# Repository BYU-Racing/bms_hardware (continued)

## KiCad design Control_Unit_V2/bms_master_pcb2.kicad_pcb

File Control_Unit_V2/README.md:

# BMS Control Unit V2 Files
This folder contains the KiCad project files for the BMS Control Unit V2.

PCB handoff from Rugby 11/10/2026 ☠️🌹⛓️

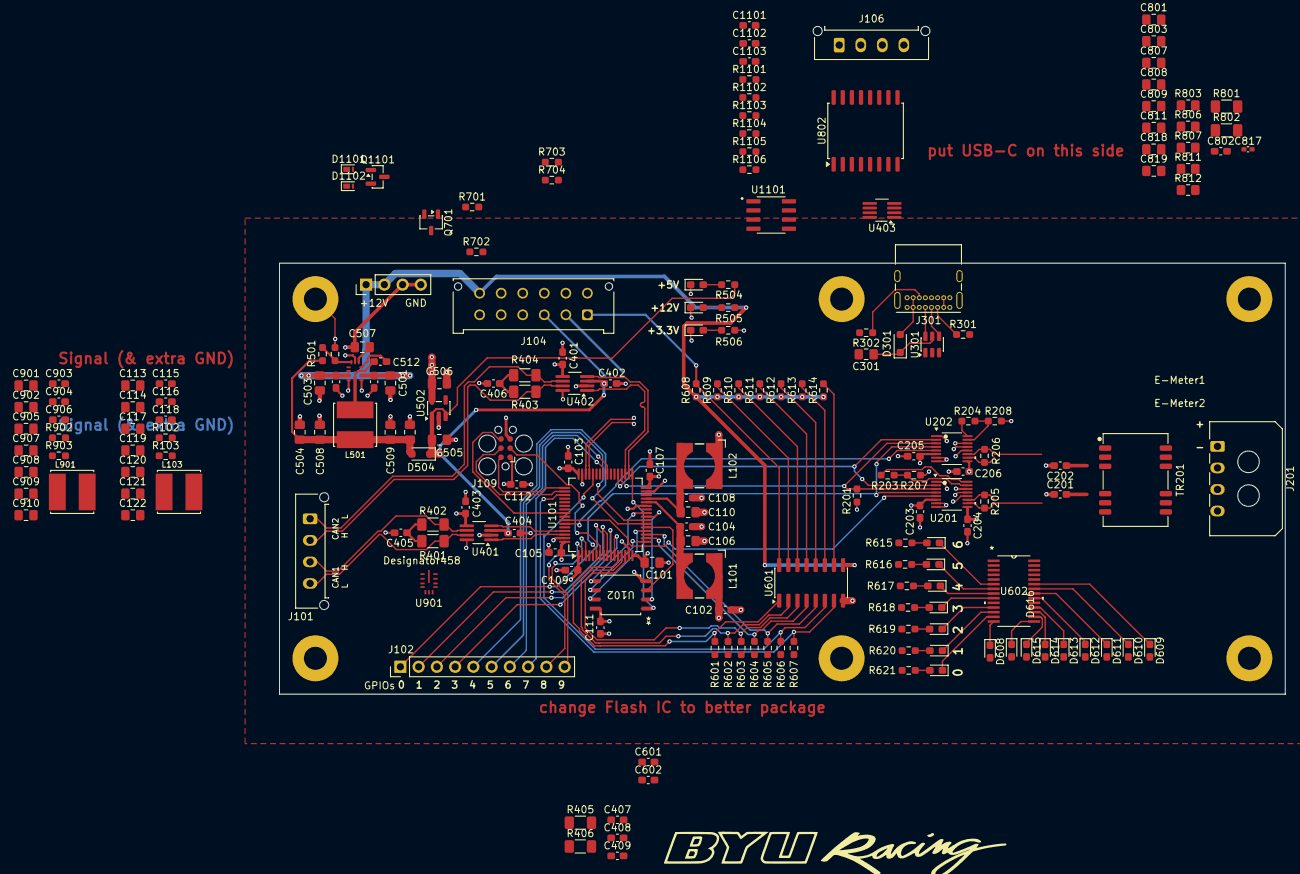
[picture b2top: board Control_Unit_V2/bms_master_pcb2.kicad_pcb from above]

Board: 4 copper layers, 140.0 x 60.0 mm, 197 parts (0 on the bottom side), 132 nets.

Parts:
C101: 4.7u; C_0805_2012Metric_Pad1.18x1.45mm_HandSolder
C102, C103, C104, C105, C107, C108, C109, C111, C112, C203, C204, C205, C206, C401, C402, C403, C404, C407, C408: 100n; C_0603_1608Metric_Pad1.08x0.95mm_HandSolder
C106, C110, C117, C505, C506, C507, C905: 1u; C_0805_2012Metric_Pad1.18x1.45mm_HandSolder
C113, C114, C301, C501, C503, C807, C818, C819, C901, C902: 10u; C_0805_2012Metric_Pad1.18x1.45mm_HandSolder
C115, C116, C510, C511, C903, C904: 220n; C_0603_1608Metric_Pad1.08x0.95mm_HandSolder
C118, C512, C906: 0.1u; C_0603_1608Metric_Pad1.08x0.95mm_HandSolder
C119, C120, C121, C122, C502, C504, C508, C509, C907, C908, C909, C910: 22u; C_0805_2012Metric_Pad1.18x1.45mm_HandSolder
C201, C202: 27p; C_0603_1608Metric_Pad1.08x0.95mm_HandSolder
C405, C406, C409, C802: 240p; C_0603_1608Metric_Pad1.08x0.95mm_HandSolder
C601: .1u; C_0603_1608Metric_Pad1.08x0.95mm_HandSolder
C602: 4.7u; C_0603_1608Metric_Pad1.08x0.95mm_HandSolder
C801, C803, C808: 100n; C_0805_2012Metric_Pad1.18x1.45mm_HandSolder
C809: 330p; C_0805_2012Metric_Pad1.18x1.45mm_HandSolder
C811: 2.2uF; C_0805_2012Metric_Pad1.18x1.45mm_HandSolder
C817: 0.1u; C_0402_1005Metric_Pad0.74x0.62mm_HandSolder
C1101: 21pf; C_0603_1608Metric_Pad1.08x0.95mm_HandSolder
C1102: 100nf; C_0603_1608Metric_Pad1.08x0.95mm_HandSolder
C1103: 0.1uf; C_0603_1608Metric_Pad1.08x0.95mm_HandSolder
D301, D504: 1N4448WS; D_SOD-323_HandSoldering
D501: 5V LED; LED_0603_1608Metric_Pad1.05x0.95mm_HandSolder
D502: 12V LED; LED_0603_1608Metric_Pad1.05x0.95mm_HandSolder
D503: 3.3V LED; LED_0603_1608Metric_Pad1.05x0.95mm_HandSolder
D601, D602, D603, D604, D605, D606, D607, D608, D609, D610, D611, D612, D613, D614, D615, D616: LED_Small; LED_0603_1608Metric_Pad1.05x0.95mm_HandSolder
D1101: Comchip ATV04A120J-HF; Nexperia_DSN1608-2_1.6x0.8mm
D1102: Vishay VTVS5V0ASMF-HM3-08; Nexperia_DSN1608-2_1.6x0.8mm
H101, H102, H103, H104, H105, H106: MountingHole; MountingHole_3.2mm_M3_Pad
J101, J106: CAN Connector; Molex_Micro-Fit_3.0_43650-0415_1x04_P3.00mm_Vertical
J102: GPIO; PinHeader_1x10_P2.54mm_Vertical
J103: EXTRA POWER IN; PinHeader_1x04_P2.54mm_Vertical
J104: Connector to GLV plug; Molex_Micro-Fit_3.0_43045-1212_2x06_P3.00mm_Vertical
J109: TC2030; Tag-Connect_TC2030-IDC-FP_2x03_P1.27mm_Vertical
J201: isoSPI Daisy Chain; Molex_Micro-Fit_3.0_43650-0400_1x04_P3.00mm_Horizontal
J301: USB4085-GF-A; USB_C_Receptacle_GCT_USB4085
L101, L102: 100u; WE-HEPC_6030
L103, L501, L901: 10u; IND_SRN6045TA-2R2Y
Q701: AO3400A; SOT-23-3
Q1101: 2N7002; SOT-23
R102, R501, R902: 100k; R_0603_1608Metric_Pad0.98x0.95mm_HandSolder
R103, R502, R903: 24.9k; R_0603_1608Metric_Pad0.98x0.95mm_HandSolder
R201, R1106: 2K; R_0603_1608Metric_Pad0.98x0.95mm_HandSolder
R203, R204, R207, R208, R506: 1k; R_0603_1608Metric_Pad0.98x0.95mm_HandSolder
R205, R206, R701: 100; R_0603_1608Metric_Pad0.98x0.95mm_HandSolder
R301, R302: 5.1K; R_0603_1608Metric_Pad0.98x0.95mm_HandSolder
R401, R402, R403, R404, R405, R406, R801, R802: 60; R_1206_3216Metric_Pad1.30x1.75mm_HandSolder
R504: 2.2k; R_0603_1608Metric_Pad0.98x0.95mm_HandSolder
R505, R615, R616, R617, R618, R619, R620, R621: 4.7k; R_0603_1608Metric_Pad0.98x0.95mm_HandSolder
R601, R602, R603, R604, R606, R607, R608, R609, R610, R611, R612, R613, R614, R702: 10K; R_0603_1608Metric_Pad0.98x0.95mm_HandSolder
R605: 720; R_0603_1608Metric_Pad0.98x0.95mm_HandSolder
R703: 470; R_0603_1608Metric_Pad0.98x0.95mm_HandSolder
R704: 100K; R_0603_1608Metric_Pad0.98x0.95mm_HandSolder
R803, R812: 10k; R_0805_2012Metric_Pad1.20x1.40mm_HandSolder
R806: 38k ±0.1%; R_0805_2012Metric_Pad1.20x1.40mm_HandSolder
R807: 10k ±0.1%; R_0805_2012Metric_Pad1.20x1.40mm_HandSolder
R811: 30k; R_0805_2012Metric_Pad1.20x1.40mm_HandSolder
R1101: 1.3K; R_0603_1608Metric_Pad0.98x0.95mm_HandSolder
R1102: 75K; R_0603_1608Metric_Pad0.98x0.95mm_HandSolder
R1103: 25K; R_0603_1608Metric_Pad0.98x0.95mm_HandSolder
R1104: 330R; R_0603_1608Metric_Pad0.98x0.95mm_HandSolder
R1105: 720R; R_0603_1608Metric_Pad0.98x0.95mm_HandSolder
TR201: TG110-E050N5xx; Transformer_HM0068ANL
U101: STM32G474RETx; LQFP-64_10x10mm_P0.5mm
U102: SST26VF064B-104V/MF; SOIJ8_SM_MCH
U201, U202: LTC6820HMS-TRPBF; MS_05-08-1669_ADI
U301: USBLC6-2SC6; SOT-23-6
U401, U402, U403: TCAN1044AVDDFRQ1; TSOT-23-8_HandSoldering
U502: AP2112K-3.3; SOT-23-5
U503, U901: LMR33620CQ5RNXRQ1; RNX0012B
U601: TPL7407LAD; SOIC-16_3.9x9.9mm_P1.27mm
U602: TLC59116IPWTQ1; PW28
U802: TJA1052i-1; SOIC-16W_7.5x10.3mm_P1.27mm
U1101: TLV9002QDRQ1; SOIC127P599X175-8N

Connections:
+3.3V: C101.1, C102.1, C103.1, C105.1, C107.1, C109.1, C111.1, C112.1, C203.1, C204.1, C205.1, C206.1, C401.1, C403.1, C407.1, C506.1, C1103.1, J104.2, J109.1, L101.1, L102.1, R201.2, R506.1, U101.1 (VBAT), U101.16 (VDD), U101.32 (VDD), U101.48 (VDD), U101.64 (VDD), U102.8 (VCC), U201.1 (EN), U201.6 (VDDS), U201.9 (VDD), U201.12 (MSTR), U202.1 (EN), U202.6 (VDDS), U202.9 (VDD), U202.12 (MSTR), U401.5 (VIO), U402.5 (VIO), U403.5 (VIO), U502.5 (VOUT), U602.28 (VCC), U1101.8 (V+)
+5V: C301.1, C402.1, C404.1, C408.1, C505.1, C803.1, C907.1, C908.1, C909.1, C910.1, D301.1 (K), D504.1 (K), L901.2, R504.1, R902.2, R1104.1, U301.5 (VBUS), U401.3 (VCC), U402.3 (VCC), U403.3 (VCC), U502.1 (VIN), U502.3 (EN), U802.1 (VDD1)
+5V_ISO: C119.1, C120.1, C121.1, C122.1, C801.1, J106.1, L103.2, R102.2, U802.11 (VDD2), U802.16 (VDD2)
+12V: C501.1, C503.1, C510.2, C511.2, C601.1, C602.1, C817.1, C818.2, C819.2, C901.1, C902.1, C903.2, C904.2, D601.2 (A), D602.2 (A), D603.2 (A), D604.2 (A), D605.2 (A), D606.2 (A), D607.2 (A), D608.2 (A), D609.2 (A), D610.2 (A), D611.2 (A), D612.2 (A), D613.2 (A), D614.2 (A), D615.2 (A), D616.2 (A), J103.1, J103.2, J104.12, R505.1, R608.1, R609.1, R610.1, R611.1, R612.1, R613.1, R614.1, R615.1, R616.1, R617.1, R618.1, R619.1, R620.1, R621.1, R703.1, R811.1, U503.2 (VIN), U503.9 (EN), U503.10 (VIN), U601.9 (COM), U901.2 (VIN), U901.9 (EN), U901.10 (VIN)
+12V_ISO: C113.1, C114.1, C115.2, C116.2, C807.2, C808.1, C811.2, R803.2, R806.2
/BMS SD STATUS: J104.1, R608.2, U601.16 (OUT1)
/BOOT0: J104.3, R704.1, U101.61 (FDCAN1_RX), U401.1 (TXD)
/BOOT_IND: R701.1, U101.14 (PA2)
/BOOT_LIGHT_CTL: J104.5, Q701.2 (D)
/BOOT_LIGHT_PWR: J104.4, R703.2
/CAN2_RX: U101.34 (FDCAN2_RX), U402.4 (RXD)
/CAN2_TX: U101.35 (FDCAN2_TX), U402.1 (TXD)
/CAN3_RX: U101.42 (FDCAN3_RX), U403.4 (RXD), U802.5 (RXD)
/CAN3_TX: U101.57 (FDCAN3_TX), U403.1 (TXD), U802.3 (TXD)
/CAN/CAN1_RX: U101.62 (FDCAN1_TX), U401.4 (RXD)
/CAN/CAN.1+: J101.2, R401.1, U401.7 (CANH)
/CAN/CAN.1-: J101.1, R402.1, U401.6 (CANL)
/CAN/CAN.2+: J101.4, R403.1, R405.1, U402.7 (CANH), U403.7 (CANH)
/CAN/CAN.2-: J101.3, R404.1, R406.1, U402.6 (CANL), U403.6 (CANL)
/CHARGE_CP: D1101.1 (K), J104.7, R1101.2, R1102.2
/CHARGE_ENAB: Q1101.1 (G), U101.60 (PB7)
/CHARGE_PILOT: U101.30 (PB10), U1101.1, U1101.2
/CHARGE_PP: D1102.1 (K), J104.6, R1104.2, R1105.1
/CHARGE_PROX: U101.26 (PB2), U1101.6, U1101.7
/CURRENT SENSE/ISO_CAN.1+: R801.1, U802.13 (CANH)
/CURRENT SENSE/ISO_CAN.1-: R802.1, U802.12 (CANL)
/DIG_OUT_0: R601.1, U601.1 (IN1)
/DIG_OUT_1: R602.1, U101.13 (PA1), U601.2 (IN2)
/DIG_OUT_2: R603.1, U101.44 (PA10), U601.3 (IN3)
/DIG_OUT_3: R604.1, U601.4 (IN4)
/DIG_OUT_5: R606.1, U601.6 (IN6)
/DIG_OUT_6: R607.1, U601.7 (IN7)
/Digital Outputs and Happy Lights/BMS_OUT_1: R609.2, U601.15 (OUT2)
/Digital Outputs and Happy Lights/BMS_OUT_2: R610.2, U601.14 (OUT3)
/Digital Outputs and Happy Lights/BMS_OUT_3: R611.2, U601.13 (OUT4)
/Digital Outputs and Happy Lights/BMS_OUT_4: R612.2, U601.12 (OUT5)
/Digital Outputs and Happy Lights/BMS_OUT_5: R613.2, U601.11 (OUT6)
/Digital Outputs and Happy Lights/BMS_OUT_6: R614.2, U601.10 (OUT7)
/GPIO_0: J102.1, U101.8 (PC0)
/GPIO_1: J102.2, U101.9 (PC1)
/GPIO_2: J102.3, U101.10 (PC2)
/GPIO_3: J102.4, U101.11 (PC3)
/GPIO_4: J102.5, U101.22 (PC4)
/GPIO_5: J102.6, U101.23 (PC5)
/GPIO_6: J102.7, U101.40 (PC8)
/GPIO_7: J102.8, U101.41 (PC9)
/GPIO_8: J102.9, U101.2 (PC13)
/GPIO_9: J102.10, U101.3 (PC14)
/LED_RESET: U101.19 (PA5), U602.25 (*RESET)
/LED_SCL: U101.38 (I2C4_SCL), U602.26 (SCL)
/LED_SDA: U101.39 (I2C4_SDA), U602.27 (SDA)
/QSPI.CLK: U101.17 (QUADSPI1_CLK), U102.6 (SCK)
/QSPI.IO0: U101.25 (QUADSPI1_BK1_IO0), U102.5 (IO0)
/QSPI.IO1: U101.24 (QUADSPI1_BK1_IO1), U102.2 (IO1)
/QSPI.IO2: U101.21 (QUADSPI1_BK1_IO2), U102.3 (IO2)
/QSPI.IO3: U101.20 (QUADSPI1_BK1_IO3), U102.7 (IO3)
/QSPI.NCS: U101.33 (QUADSPI1_BK1_NCS), U102.1 (CE#)
/RESET: J109.3, U101.7 (RCC_MCO)
/SPI_CS1: U101.58 (PB5), U201.5 (*CS)
/SPI_CS2: U101.59 (PB6), U202.5 (*CS)
/SWCLK: J109.4, U101.50 (SYS_JTCK-SWCLK)
/SWDIO: J109.2, U101.49 (SYS_JTMS-SWDIO)
/SWO: J109.6, U101.56 (SYS_JTDO-SWO)
/USB/D+: J301.A6 (D+), J301.B6 (D+), U301.4 (I/O2)
/USB/D-: J301.A7 (D-), J301.B7 (D-), U301.6 (I/O1)
/USB/USB.D+: U101.46 (USB_DP), U301.3 (I/O2)
/USB/USB.D-: U101.45 (USB_DM), U301.1 (I/O1)
/isoSPI/INPUT_isoSPI.D+: J201.3, TR201.12 (RX+)
/isoSPI/INPUT_isoSPI.D-: J201.4, TR201.11 (RX-)
/isoSPI/OUTPUT_isoSPI.D+: J201.1, TR201.8 (TX+)
/isoSPI/OUTPUT_isoSPI.D-: J201.2, TR201.7 (TX-)
/isoSPI/SPI2.MISO: R201.1, U101.36 (SPI2_MISO), U201.3 (MISO), U202.3 (MISO)
/isoSPI/SPI2.MOSI: U101.37 (SPI2_MOSI), U201.2 (MOSI), U202.2 (MOSI)
/isoSPI/SPI2.SCK: U101.6 (SPI2_SCK), U201.4 (SCK), U202.4 (SCK)
/isoSPI/isoSPI.D+: R205.2, TR201.1 (RD+), U201.11 (IP)
/isoSPI/isoSPI.D-: R205.1, TR201.2 (RD-), U201.10 (IM)
/isoSPI/isoSPI_2.D+: R206.2, TR201.5 (TD+), U202.11 (IP)
/isoSPI/isoSPI_2.D-: R206.1, TR201.6 (TD-), U202.10 (IM)
GND: C101.2, C102.2, C103.2, C104.2, C105.2, C106.2, C107.2, C108.2, C109.2, C110.2, C111.2, C112.2, C201.2, C202.2, C203.2, C204.2, C205.2, C206.2, C301.2, C401.2, C402.2, C403.2, C404.2, C405.2, C406.2, C407.2, C408.2, C409.2, C501.2, C502.2, C503.2, C504.2, C505.2, C506.2, C507.2, C508.2, C509.2, C510.1, C511.1, C601.2, C602.2, C803.2, C817.2, C818.1, C819.1, C901.2, C902.2, C903.1, C904.1, C905.2, C907.2, C908.2, C909.2, C910.2, C1101.2, C1102.2, C1103.2, D501.1 (K), D502.1 (K), D503.1 (K), D1101.2 (A), D1102.2 (A), H101.1 (1_1), H102.1 (1_1), H103.1 (1_1), H104.1 (1_1), H105.1 (1_1), H106.1 (1_1), J103.3, J103.4, J104.11, J109.5, J301.A1 (GND), J301.A12 (GND), J301.B1 (GND), J301.B12 (GND), J301.SH (SHIELD), Q701.3 (S), Q1101.3 (D), R207.2, R208.2, R301.2, R302.2, R502.1, R601.2, R602.2, R603.2, R604.2, R605.1, R606.2, R607.2, R702.2, R704.2, R812.2, R903.1, R1103.1, R1106.2, U101.15 (VSS), U101.27 (VSSA), U101.31 (VSS), U101.47 (VSS), U101.63 (VSS), U102.4 (VSS), U201.7 (POL), U201.8 (PHA), U201.13 (SLOW), U201.14 (GND), U202.7 (POL), U202.8 (PHA), U202.13 (SLOW), U202.14 (GND), U301.2 (GND), U401.2 (GND), U401.8 (STB), U402.2 (GND), U402.8 (STB), U403.2 (GND), U403.8 (STB), U502.2 (GND), U503.1 (PGND), U503.6 (AGND), U503.11 (PGND), U601.8 (GND), U602.2 (A0), U602.3 (A1), U602.4 (A2), U602.5 (A3), U602.10 (GND), U602.19 (GND), U602.24 (GND), U901.1 (PGND), U901.6 (AGND), U901.11 (PGND), U1101.4 (V-)
HV-: C113.2, C114.2, C115.1, C116.1, C117.2, C119.2, C120.2, C121.2, C122.2, C801.2, C802.2, C807.1, C808.2, C809.2, C811.1, R103.1, R807.1, U802.9 (GND2), U802.10 (GND2), U802.14 (STB), U802.15 (GND2)
unnamed: C405.1, R401.2, R402.2
unnamed: C406.1, R403.2, R404.2
unnamed: C409.1, R405.2, R406.2
unnamed: C802.1, R801.2, R802.2
unnamed: C1101.1, R1102.1, R1103.2, U1101.3
unnamed: C1102.1, R1105.2, R1106.1, U1101.5
unnamed: D301.2 (A), J301.A4 (VBUS), J301.A9 (VBUS), J301.B4 (VBUS), J301.B9 (VBUS)
unnamed: D501.2 (A), R504.2
unnamed: D502.2 (A), R505.2
unnamed: D503.2 (A), R506.2
unnamed: C502.1, C504.1, C508.1, C509.1, D504.2 (A), L501.2, R501.2
unnamed: D601.1 (K), U602.6 (*OUT0)
unnamed: D602.1 (K), U602.7 (*OUT1)
unnamed: D603.1 (K), U602.8 (*OUT2)
unnamed: D604.1 (K), U602.9 (*OUT3)
unnamed: D605.1 (K), U602.11 (*OUT4)
unnamed: D606.1 (K), U602.12 (*OUT5)
unnamed: D607.1 (K), U602.13 (*OUT6)
unnamed: D608.1 (K), U602.14 (*OUT7)
unnamed: D609.1 (K), U602.23 (*OUT15)
unnamed: D610.1 (K), U602.22 (*OUT14)
unnamed: D611.1 (K), U602.21 (*OUT13)
unnamed: D612.1 (K), U602.20 (*OUT12)
unnamed: D613.1 (K), U602.18 (*OUT11)
unnamed: D614.1 (K), U602.17 (*OUT10)
unnamed: D615.1 (K), U602.16 (*OUT9)
unnamed: D616.1 (K), U602.15 (*OUT8)
unnamed: J301.A5 (CC1), R301.1
unnamed: J301.B5 (CC2), R302.1
unnamed: Q701.1 (G), R701.2, R702.1
unnamed: Q1101.2 (S), R1101.1
unnamed: C201.1, TR201.3 (RDCT)
unnamed: C202.1, TR201.4 (TDCT)
unnamed: C108.1, C110.1, L102.2, U101.29 (VDDA)
unnamed: C104.1, C106.1, L101.2, U101.28 (VREF+)
unnamed: R102.1, R103.2
unnamed: C118.1, L103.1
unnamed: R203.1, U201.16 (IBIAS)
unnamed: R203.2, R207.1, U201.15 (ICMP)
unnamed: R204.1, U202.16 (IBIAS)
unnamed: R204.2, R208.1, U202.15 (ICMP)
unnamed: C512.2, U503.4 (BOOT)
unnamed: R501.1, R502.2, U503.7 (FB)
unnamed: C512.1, L501.1, U503.3 (NC), U503.12 (SW)
unnamed: C507.1, U503.5 (VCC)
unnamed: R605.2, U602.1 (REXT)
unnamed: R811.2, R812.1
unnamed: C809.1, R806.1, R807.2
unnamed: C906.2, U901.4 (BOOT)
unnamed: R902.1, R903.2, U901.7 (FB)
unnamed: C906.1, L901.1, U901.3 (NC), U901.12 (SW)
unnamed: C905.1, U901.5 (VCC)

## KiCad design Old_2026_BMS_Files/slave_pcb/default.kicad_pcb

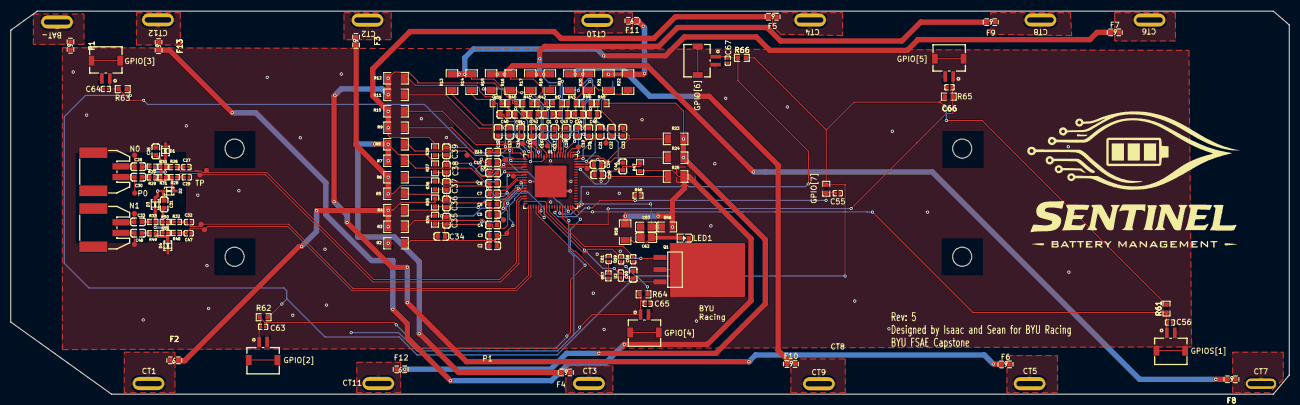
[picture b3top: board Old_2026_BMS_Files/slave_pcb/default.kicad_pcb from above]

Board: 2 copper layers, 241.0 x 72.2 mm, 184 parts (0 on the bottom side), 98 nets.

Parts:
C1, C34, C35, C36, C37, C38, C39, C40, C41, C42, C43, C44, C45, C46: 10nF ±10% 50V X7R; C0603
C2, C3, C4, C5, C6, C7, C8, C9, C10, C11, C12, C13, C14, C15, C16, C17, C18, C19, C20, C21, C22, C23, C24, C25, C26, C31: 100nF ±10% 50V X7R; C0603
C27, C29, C32, C47: 330pF ±10% 50V X7R; C0402
C28, C30, C33, C48: 22nF ±10% 50V X7R; C0603
C55, C56, C63, C64, C65, C66, C67: 100nF ±10% 16V X7R; C0402
C57: 10nF ±10% 50V X7R; C0805
C58, C59: 1µF ±10% 25V X5R; C0402
C60: 1µF ±10% 50V X5R; C0603
C61: 10nF ±10% 50V X7R; C0402
C62: 10nF ±10% 100V X7R; C0805
CN1, CN2: CONN-SMD-2P_5023520200
CN3, CN4, CN5, CN6, CN7, CN8: CONN-SMD_S2B-ZR-SM4A
D1, D2, D3, D4: SOD-323_L1.8-W1.3-LS2.5-BI
F1, F2, F3, F4, F5, F6, F7, F8, F9, F10, F11, F12, F13: F0603
LED1: LED0603-RD
Q1: SOT-223-4_L6.5-W3.5-P2.30-LS7.0-BR
R1, R34, R35, R36, R37, R38, R39, R40, R41, R42, R43, R44, R45, R47: 200Ω ±1% 100mW; R0603
R2, R3, R4, R5, R6, R7, R8, R9, R10, R11, R12, R13, R14, R15, R16, R17, R18, R19, R20, R21, R22, R23, R24, R25: 22Ω ±1% 250mW; R1206
R26, R28, R32, R48: 22Ω ±1% 62.5mW; R0402
R27, R29, R33, R49: 15Ω ±1% 62.5mW; R0402
R30, R31, R50, R51: 43Ω ±1% 62.5mW; R0402
R46: R0402
R56: 1kΩ ±1% 125mW; R0805
R57: 10Ω ±1% 62.5mW; R0402
R58: 330Ω ±5% 250mW; R1206
R60, R61, R62, R63, R64, R65, R66: 10kΩ ±1% 100mW; R0603
TP1, TP2, TP3, TP4, TP5, TP6, TP7, TP8, TP9, TP10, TP11, TP12, TP13: voltage_tap
TP14, TP15, TP16, TP17, TP18, TP19, TP20, TP21, TP22, TP23, TP24, TP25, TP26, TP27, TP28, TP29, TP30, TP31, TP32, TP33: TestPoint_Pad_D1.0mm
U1: QFN-72_L10.0-W10.0-P0.50-BL-EP6.0_1
U2: L0402

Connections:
A: C62.1, LED1.2, R58.2
C0: C34.1, C35.2, R34.2, U1.50
C1: C35.1, C36.2, R35.2, U1.48
C2: C36.1, C37.2, R36.2, U1.45
C3: C37.1, C38.2, R37.2, U1.42
C4: C38.1, C39.2, R38.2, U1.39
C5: C39.1, C40.2, R39.2, U1.36
C6: C40.1, C41.2, R40.2, U1.33
C7: C41.1, C42.2, R41.2, U1.30
C8: C1.2, C42.1, R42.2, U1.27
C9: C43.1, C44.2, R43.2, U1.23
C9N: C1.1, C43.2, R1.2, U1.26
C10: C44.1, C45.2, R44.2, U1.20
C11: C45.1, C46.2, R45.2, U1.17
C12: C46.1, R47.2, U1.14
DRIVE: R57.1, U1.58
K: LED1.1, Q1.2, Q1.4
S1N: C2.1, C3.2, R2.2, TP22.1, U1.59
S1P: C3.1, C4.2, R3.2, U1.49
S2N: C4.1, C5.2, R4.2, TP23.1, U1.46
S2P: C5.1, C6.2, R5.2, U1.47
S3N: C6.1, C7.2, R6.2, TP24.1, U1.43
S3P: C7.1, C8.2, R7.2, U1.44
S4N: C8.1, C9.2, R8.2, TP25.1, U1.40
S4P: C9.1, C10.2, R9.2, U1.41
S5N: C10.1, C11.2, R10.2, TP26.1, U1.37
S5P: C11.1, C12.2, R11.2, U1.38
S6N: C12.1, C13.2, R12.2, TP27.1, U1.34
S6P: C13.1, C14.2, R13.2, U1.35
S7N: C14.1, C15.2, R14.2, TP28.1, U1.31
S7P: C15.1, C16.2, R15.2, U1.32
S8N: C16.1, C17.2, R16.2, TP29.1, U1.28
S8P: C17.1, C18.2, R17.2, U1.29
S9N: C18.1, C19.2, R18.2, TP30.1, U1.24
S9P: C19.1, C20.2, R19.2, U1.25
S10N: C20.1, C21.2, R20.2, TP31.1, U1.21
S10P: C21.1, C22.2, R21.2, U1.22
S11N: C22.1, C23.2, R22.2, TP32.1, U1.18
S11P: C23.1, C24.2, R23.2, U1.19
S12N: C24.1, C25.2, R24.2, TP33.1, U1.15
S12P: C25.1, R25.2, U1.16
asic_vp-VCC: C57.1, R56.2, U1.1
base: C61.1, Q1.1, R57.2
bat-: C2.2, C26.2, C27.2, C29.2, C31.2, C32.2, C34.2, C47.2, C55.2, C56.2, C57.2, C58.2, C59.2, C60.2, C61.2, C62.2, C63.2, C64.2, C65.2, C66.2, C67.2, CN3.2, CN4.2, CN5.2, CN6.2, CN7.2, CN8.2, D1.1, D2.1, D3.1, D4.1, F1.2, R2.1, R34.1, R46.2, U1.60, U1.73
cell_tap_1: F2.2, R3.1, R4.1, R35.1
cell_tap_2: F3.2, R5.1, R6.1, R36.1
cell_tap_3: F4.2, R7.1, R8.1, R37.1
cell_tap_4: F5.2, R9.1, R10.1, R38.1
cell_tap_5: F6.2, R11.1, R12.1, R39.1
cell_tap_6: F7.2, R13.1, R14.1, R40.1
cell_tap_7: F8.2, R15.1, R16.1, R41.1
cell_tap_8: F9.2, R1.1, R17.1, R18.1, R42.1
cell_tap_9: F10.2, R19.1, R20.1, R43.1
cell_tap_10: F11.2, R21.1, R22.1, R44.1
cell_tap_11: F12.2, R23.1, R24.1, R45.1
cell_tap_12: F13.2, R25.1, R47.1, R56.1, R58.1
cell_tap_fuses[0]-_1: F1.1, TP1.1
cell_tap_fuses[1]-_1: F2.1, TP2.1
cell_tap_fuses[2]-_1: F3.1, TP3.1
cell_tap_fuses[3]-_1: F4.1, TP4.1
cell_tap_fuses[4]-_1: F5.1, TP5.1
cell_tap_fuses[5]-_1: F6.1, TP6.1
cell_tap_fuses[6]-_1: F7.1, TP7.1
cell_tap_fuses[7]-_1: F8.1, TP8.1
cell_tap_fuses[8]-_1: F9.1, TP9.1
cell_tap_fuses[9]-_1: F10.1, TP10.1
cell_tap_fuses[10]-_1: F11.1, TP11.1
cell_tap_fuses[11]-_1: F12.1, TP12.1
cell_tap_fuses[12]-_1: F13.1, TP13.1
common_mode_cap-common_mode_node-0: C26.1, R30.2, R31.2
common_mode_cap-common_mode_node-1: C31.1, R50.2, R51.2
damping_resistor-point_a-0: D1.2, R26.2, R27.1, R30.1
damping_resistor-point_a-1: D2.2, R28.2, R29.1, R31.1
damping_resistor-point_a-2: D3.2, R32.2, R33.1, R50.1
damping_resistor-point_a-3: D4.2, R48.2, R49.1, R51.1
emitter: Q1.3, U2.1
footprint-net-0: C28.1, R27.2
footprint-net-1: C30.1, R29.2
footprint-net-2: C33.1, R33.2
footprint-net-3: C48.1, R49.2
gpios[0]-output_signal: C56.1, CN3.1, R61.2, U1.72
gpios[1]-output_signal: C63.1, CN4.1, R62.2, U1.71
gpios[2]-output_signal: C64.1, CN5.1, R63.2, U1.70
gpios[3]-output_signal: C65.1, CN6.1, R64.2, U1.69
gpios[4]-output_signal: C66.1, CN7.1, R65.2, U1.68
gpios[5]-output_signal: C67.1, CN8.1, R66.2, U1.67
gpios[6]-output_signal: C55.1, R46.1, R60.2, U1.66
isoA_N: C27.1, R26.1, TP15.1, U1.51
isoA_P: C29.1, R28.1, TP17.1, U1.52
isoB_N: C32.1, R32.1, TP19.1, U1.55
isoB_P: C47.1, R48.1, TP21.1, U1.56
isoSPI_filters[0]-output_pair-contact_N: C28.2, CN1.2, TP14.1
isoSPI_filters[0]-output_pair-contact_P: C30.2, CN1.1, TP16.1
isoSPI_filters[1]-output_pair-contact_N: C33.2, CN2.2, TP18.1
isoSPI_filters[1]-output_pair-contact_P: C48.2, CN2.1, TP20.1
vref1-VCC: C58.1, U1.63
vref2-VCC: C59.1, R60.1, R61.1, R62.1, R63.1, R64.1, R65.1, R66.1, U1.61
vreg-VCC: C60.1, U1.53, U1.62, U2.2

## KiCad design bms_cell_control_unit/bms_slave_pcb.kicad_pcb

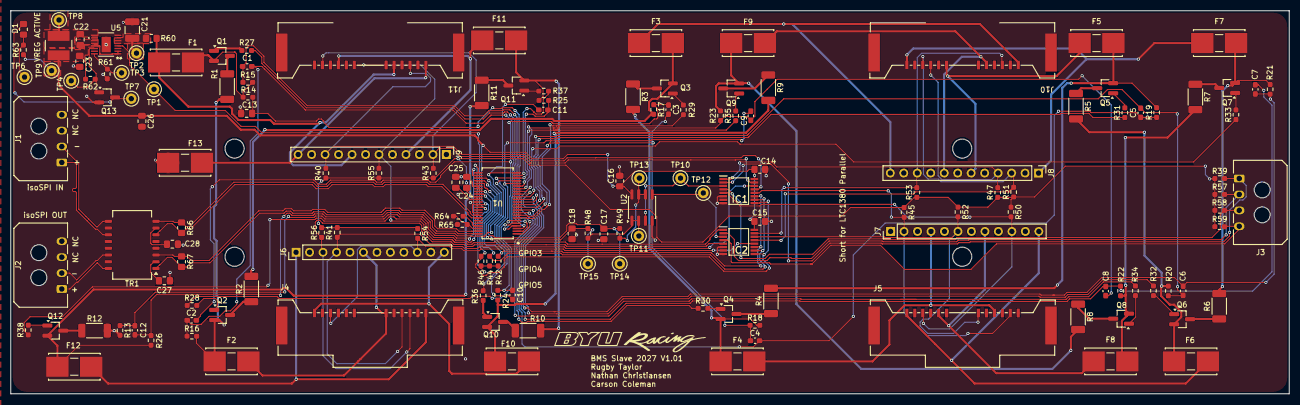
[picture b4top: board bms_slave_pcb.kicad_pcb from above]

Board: 2 copper layers, 241.0 x 72.2 mm, 152 parts (0 on the bottom side), 124 nets.

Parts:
C1, C2, C3, C4, C5, C6, C7, C8, C9, C10, C11, C12: 10nF; C_0603_1608Metric_Pad1.08x0.95mm_HandSolder
C13: 100nF; C_0805_2012Metric_Pad1.18x1.45mm_HandSolder
C14: 1uF; R_0805_2012Metric_Pad1.20x1.40mm_HandSolder
C15, C16: 1uf; R_0805_2012Metric_Pad1.20x1.40mm_HandSolder
C17, C18: 10nF; R_0805_2012Metric_Pad1.20x1.40mm_HandSolder
C21: 2.2uF; C_1210_3225Metric_Pad1.33x2.70mm_HandSolder
C22, C23: 22uF; C_0805_2012Metric_Pad1.18x1.45mm_HandSolder
C24, C25, C26: 1uF; C_0805_2012Metric_Pad1.18x1.45mm_HandSolder
C27, C28: 10nF; C_0805_2012Metric_Pad1.18x1.45mm_HandSolder
D1: LED; R_0805_2012Metric_Pad1.20x1.40mm_HandSolder
F1, F13: 500mA; Littelfuse_01550900M_Fuse_Blok_Cartridge
F2, F3, F4, F5, F6, F7, F8, F9, F10, F11, F12: 250mA; Littelfuse_01550900M_Fuse_Blok_Cartridge
IC1, IC2: TMUX1308AQPWRQ1; SOP65P640X120-16N
J1: isoSPI Daisy Chain IN; Molex_Micro-Fit_3.0_43650-0400_1x04_P3.00mm_Horizontal
J2: isoSPI Daisy Chain OUT; Molex_Micro-Fit_3.0_43650-0400_1x04_P3.00mm_Horizontal
J3: Extra Thermistor Connector; Molex_Micro-Fit_3.0_43650-0400_1x04_P3.00mm_Horizontal
J4: Module Top Left FPC Female; FPC_Female_Connector
J5: Module Top Right FPC Female; FPC_Female_Connector
J6, J7, J8, J9: Breadboard pins for testing; PinHeader_1x12_P2.54mm_Vertical
J10: Module Bottom Left FPC Female; FPC_Female_Connector
J11: Module Bottom Right FPC Female; FPC_Female_Connector
L1: 33uH; IND_LQH5BPH330MT0L
Q1, Q2, Q3, Q4, Q5, Q6, Q7, Q8, Q9, Q10, Q11, Q12: BSS308PE; SOT-23_Handsoldering
Q13: 2N7002; SOT-23_Handsoldering
R1, R2, R3, R4, R5, R6, R7, R8, R9, R10, R11, R12: 33; R_2010_5025Metric_Pad1.40x2.65mm_HandSolder
R13, R14, R15, R16, R17, R18, R19, R20, R21, R22, R23, R24, R25, R26, R48, R49: 100; R_0603_1608Metric_Pad0.98x0.95mm_HandSolder
R27, R28, R29, R30, R31, R32, R33, R34, R35, R36, R37, R38: 3.3k; R_0603_1608Metric_Pad0.98x0.95mm_HandSolder
R39, R40, R41, R43, R45, R47, R50, R51, R52, R53, R54, R55, R56, R57, R58, R59: 10k; R_0603_1608Metric_Pad0.98x0.95mm_HandSolder
R42, R44, R46: 4.7K; R_0603_1608Metric_Pad0.98x0.95mm_HandSolder
R60: 470; R_0805_2012Metric_Pad1.20x1.40mm_HandSolder
R61: 374k; R_0603_1608Metric_Pad0.98x0.95mm_HandSolder
R62: 220k; R_0603_1608Metric_Pad0.98x0.95mm_HandSolder
R63: 2.2k; R_0603_1608Metric_Pad0.98x0.95mm_HandSolder
R64, R65: 1k; R_0603_1608Metric_Pad0.98x0.95mm_HandSolder
R66, R67: 100; R_0805_2012Metric_Pad1.20x1.40mm_HandSolder
TP1, TP2, TP3, TP4, TP6, TP7, TP8, TP9, TP10, TP11, TP12, TP13, TP14, TP15: TestPoint; TestPoint_Keystone_5000-5004_Miniature
TR1: TG110I-AE050N5xx; Transformer_Ethernet_Halo_N5_SO-16_7.11x12.7mm
U1: LTC6811HGI-1I-3ZZTRPBF; 05-08-1887_ADI
U2: TLV9002IDR; SOIC-8_3.9x4.9mm_P1.27mm
U5: LT3990HMSEI-5I-PBF; MSOP-16_MSE_LIT

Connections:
/FPC Connections/TH1: IC1.13 (S0), J9.10, J11.10, R40.2
/FPC Connections/TH2: IC1.14 (S1), J4.4, J6.4, R41.2
/FPC Connections/TH3: IC1.15 (S2), J9.2, J11.2, R43.2
/FPC Connections/TH4: IC1.12 (S3), J5.2, J7.2, R45.2
/FPC Connections/TH5: IC1.1 (S4), J8.4, J10.4, R47.2
/FPC Connections/TH6: IC1.5 (S5), J5.10, J7.10, R50.2
/FPC Connections/TH7: IC2.13 (S0), J8.3, J10.3, R51.2
/FPC Connections/TH8: IC2.14 (S1), J5.6, J7.6, R52.2
/FPC Connections/TH9: IC2.15 (S2), J8.10, J10.10, R53.2
/FPC Connections/TH10: IC2.12 (S3), J4.10, J6.10, R54.2
/FPC Connections/TH11: IC2.1 (S4), J9.6, J11.6, R55.2
/FPC Connections/TH12: IC2.5 (S5), J4.3, J6.3, R56.2
/FPC Connections/VBUS1: F12.1, J4.1, J6.1
/FPC Connections/VBUS2: F11.1, J9.4, J11.4
/FPC Connections/VBUS3: F10.1, J4.12, J6.12
/FPC Connections/VBUS4: F9.1, J8.8, J10.8
/FPC Connections/VBUS5: F8.1, J5.8, J7.8
/FPC Connections/VBUS6: F7.1, J8.1, J10.1
/FPC Connections/VBUS7: F6.1, J5.12, J7.12
/FPC Connections/VBUS8: F5.1, J8.6, J10.6
/FPC Connections/VBUS9: F4.1, J5.4, J7.4
/FPC Connections/VBUS10: F3.1, J8.12, J10.12
/FPC Connections/VBUS11: F2.1, J4.6, J6.6
/FPC Connections/VBUS12: F1.1, J9.8, J11.8, R60.2
/FPC Connections/VBUS_GNDREF: F13.1, J9.12, J11.12
/Power Rail/DRIVE: TP1.1 (1_1), U1.38 (DRIVE), U5.4 (EN/UVLO)
/Power Rail/VREG: C14.1, C15.1, C16.1, C23.1, C26.1, IC1.16 (VDD), IC2.16 (VDD), L1.2, R42.1, R44.1, R46.1, R62.1, R63.1, TP9.1 (1_1), U1.37 (VREG), U1.40 (ISOMD), U2.8 (V+), U5.1 (FB/VOUT), U5.2 (FB/VOUT), U5.13 (BD)
/Temperature Sensing/GPIO1(MUX_OUT_1): C18.1, R48.1, TP15.1 (1_1), U1.27 (GPIO1)
/Temperature Sensing/GPIO2(MUX_OUT_2): C17.1, R49.1, TP14.1 (1_1), U1.28 (GPIO2)
/Temperature Sensing/GPIO3: IC1.11 (A0), IC2.11 (A0), R42.2, U1.29 (GPIO3)
/Temperature Sensing/GPIO4: IC1.10 (A1), IC2.10 (A1), R44.2, U1.32 (GPIO4)
/Temperature Sensing/GPIO5: IC1.9 (A2), IC2.9 (A2), R46.2, U1.33 (GPIO5)
/Temperature Sensing/TH0: IC1.2 (S6), J3.1, R39.2
/Temperature Sensing/TH13: IC2.2 (S6), J3.2, R57.2
/Temperature Sensing/TH14: IC1.4 (S7), J3.3, R58.2
/Temperature Sensing/TH15: IC2.4 (S7), J3.4, R59.2
/Temperature Sensing/V_REF2: C24.1, R39.1, R40.1, R41.1, R43.1, R45.1, R47.1, R50.1, R51.1, R52.1, R53.1, R54.1, R55.1, R56.1, R57.1, R58.1, R59.1, U1.34 (VREF2)
/Voltage Taps/C0: C12.2, R13.1, U1.26 (C0)
/Voltage Taps/C1: C11.2, C12.1, R26.1, U1.24 (C1)
/Voltage Taps/C2: C10.2, C11.1, R25.1, U1.22 (C2)
/Voltage Taps/C3: C9.2, C10.1, R24.1, U1.20 (C3)
/Voltage Taps/C4: C8.2, C9.1, R23.1, U1.18 (C4)
/Voltage Taps/C5: C7.2, C8.1, R22.1, U1.16 (C5)
/Voltage Taps/C6: C6.2, C7.1, R21.1, U1.14 (C6)
/Voltage Taps/C7: C5.2, C6.1, R20.1, U1.12 (C7)
/Voltage Taps/C8: C4.2, C5.1, R19.1, U1.10 (C8)
/Voltage Taps/C9: C3.2, C4.1, R18.1, U1.8 (C9)
/Voltage Taps/C10: C2.2, C3.1, R17.1, U1.6 (C10)
/Voltage Taps/C11: C1.2, C2.1, R16.1, U1.4 (C11)
/Voltage Taps/C12: C1.1, R15.1, U1.2 (C12)
/Voltage Taps/S1: R38.1, U1.25 (S1)
/Voltage Taps/S2: R37.1, U1.23 (S2)
/Voltage Taps/S3: R36.1, U1.21 (S3)
/Voltage Taps/S4: R35.1, U1.19 (S4)
/Voltage Taps/S5: R34.1, U1.17 (S5)
/Voltage Taps/S6: R33.1, U1.15 (S6)
/Voltage Taps/S7: R32.1, U1.13 (S7)
/Voltage Taps/S8: R31.1, U1.11 (S8)
/Voltage Taps/S9: R30.1, U1.9 (S9)
/Voltage Taps/S10: R29.1, U1.7 (S10)
/Voltage Taps/S11: R28.1, U1.5 (S11)
/Voltage Taps/S12: R27.1, U1.3 (S12)
/Voltage Taps/VI+: C13.1, R14.1, U1.1 (V+)
/isoSPI Daisy Chain/+: R66.2, TR1.6 (RX-), U1.42 (SCK(IPA))
/isoSPI Daisy Chain/-: R66.1, TR1.8 (RX+), U1.41 (CSB(IMA))
/isoSPI Daisy Chain/I+: R67.2, TR1.1 (TX-), U1.48 (IPB)
/isoSPI Daisy Chain/I-: R67.1, TR1.3 (TX+), U1.47 (IMB)
/isoSPI Daisy Chain/IBIAS: R64.2, U1.45 (IBIAS)
/isoSPI Daisy Chain/ICMP: R64.1, R65.2, U1.46 (ICMP)
/isoSPI Daisy Chain/V_REF1: C25.1, U1.35 (VREF1)
/isoSPI Daisy Chain/isoSPIAI+: J1.1, TR1.11 (RD-)
/isoSPI Daisy Chain/isoSPIAI-: J1.2, TR1.9 (RD+)
/isoSPI Daisy Chain/isoSPIBI+: J2.1, TR1.16 (TD-)
/isoSPI Daisy Chain/isoSPIBI-: J2.2, TR1.14 (TD+)
GNDREF: C13.2, C14.2, C15.2, C16.2, C17.2, C18.2, C21.2, C23.2, C24.2, C25.2, C26.2, C27.2, C28.2, F13.2, IC1.6 (~EN), IC1.8 (GND), IC2.6 (~EN), IC2.8 (GND), J4.2, J4.5, J4.7, J4.9, J4.11, J5.1, J5.3, J5.5, J5.7, J5.9, J5.11, J6.2, J6.5, J6.7, J6.9, J6.11, J7.1, J7.3, J7.5, J7.7, J7.9, J7.11, J8.2, J8.5, J8.7, J8.9, J8.11, J9.1, J9.3, J9.5, J9.7, J9.9, J9.11, J10.2, J10.5, J10.7, J10.9, J10.11, J11.1, J11.3, J11.5, J11.7, J11.9, J11.11, Q13.2 (S), R12.2, R13.2, R61.2, R65.1, U1.30 (V-), U1.31 (V-), U1.36 (DTEN), U2.4 (V-), U5.8 (GND), U5.17
unnamed: D1.2 (A), R63.2, TP6.1 (1_1)
unnamed: D1.1 (K), Q13.3 (D), TP7.1 (1_1)
unnamed: IC1.3 (D), TP10.1 (1_1), U2.3
unnamed: IC2.3 (D), TP12.1 (1_1), U2.5
unnamed: Q1.3 (D), R1.1
unnamed: Q1.1 (G), R27.2
unnamed: F1.2, Q1.2 (S), R14.2, R15.2
unnamed: Q2.3 (D), R2.1
unnamed: Q2.1 (G), R28.2
unnamed: F2.2, Q2.2 (S), R1.2, R16.2
unnamed: Q3.3 (D), R3.1
unnamed: Q3.1 (G), R29.2
unnamed: F3.2, Q3.2 (S), R2.2, R17.2
unnamed: Q4.3 (D), R4.1
unnamed: Q4.1 (G), R30.2
unnamed: F4.2, Q4.2 (S), R3.2, R18.2
unnamed: Q5.3 (D), R5.1
unnamed: Q5.1 (G), R31.2
unnamed: F5.2, Q5.2 (S), R4.2, R19.2
unnamed: Q6.3 (D), R6.1
unnamed: Q6.1 (G), R32.2
unnamed: F6.2, Q6.2 (S), R5.2, R20.2
unnamed: Q7.3 (D), R7.1
unnamed: Q7.1 (G), R33.2
unnamed: F7.2, Q7.2 (S), R6.2, R21.2
unnamed: Q8.3 (D), R8.1
unnamed: Q8.1 (G), R34.2
unnamed: F8.2, Q8.2 (S), R7.2, R22.2
unnamed: Q9.3 (D), R9.1
unnamed: Q9.1 (G), R35.2
unnamed: F9.2, Q9.2 (S), R8.2, R23.2
unnamed: Q10.3 (D), R10.1
unnamed: Q10.1 (G), R36.2
unnamed: F10.2, Q10.2 (S), R9.2, R24.2
unnamed: Q11.3 (D), R11.1
unnamed: Q11.1 (G), R37.2
unnamed: F11.2, Q11.2 (S), R10.2, R25.2
unnamed: Q12.3 (D), R12.1
unnamed: Q12.1 (G), R38.2
unnamed: F12.2, Q12.2 (S), R11.2, R26.2
unnamed: Q13.1 (G), R62.2, TP4.1 (1_1), U5.14 (PG)
unnamed: R48.2, TP11.1 (1_1), U2.1, U2.2
unnamed: R49.2, TP13.1 (1_1), U2.6, U2.7
unnamed: C28.1, TR1.7 (C_RX)
unnamed: C27.1, TR1.2 (C_TX)
unnamed: C22.1, U5.11 (BOOST)
unnamed: R61.1, TP3.1 (1_1), U5.16 (RT)
unnamed: C22.2, L1.1, TP8.1 (1_1), U5.9 (SW)
unnamed: C21.1, R60.1, TP2.1 (1_1), U5.6 (VIN)

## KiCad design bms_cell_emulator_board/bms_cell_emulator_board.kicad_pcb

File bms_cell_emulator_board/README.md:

# BMS Cell Emulator V1
These are the KiCad PCB files relating to Nathan Christiansen's V1 for a PCB designed to emulate 
the battery cells of an individual module. With something similar to this we can test the Cell Monitor PCBs 
and the Main Control Unit for the BMS without the need to plug those PCBs into the battery first. We can
safely test those different parts of the BMS before we plug them into live battery cells.

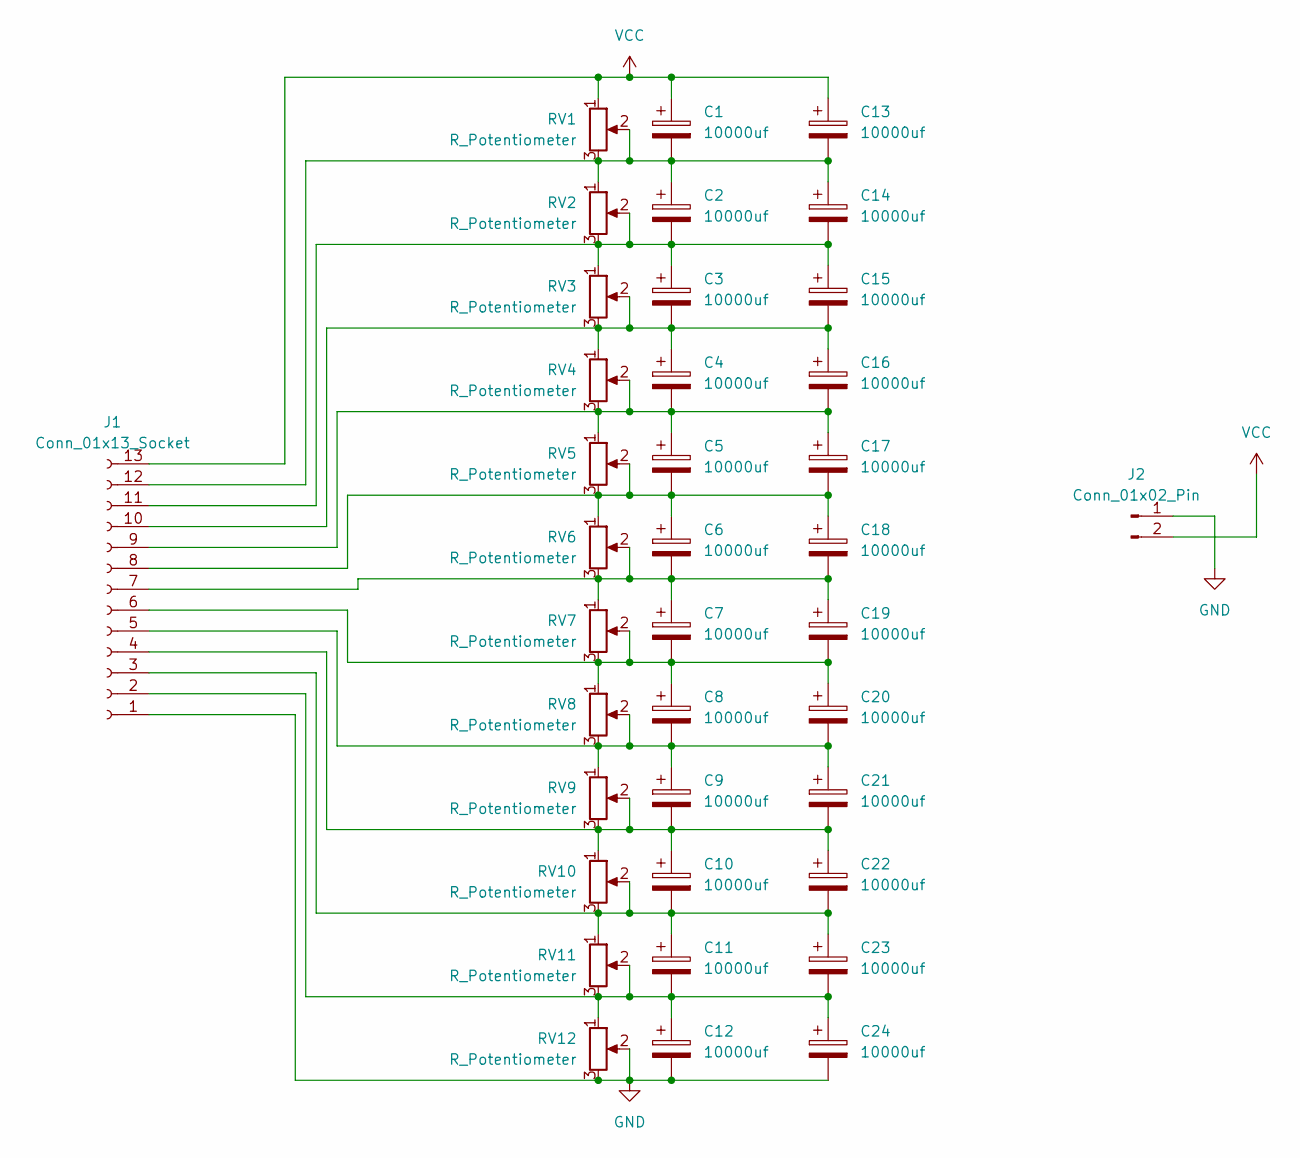
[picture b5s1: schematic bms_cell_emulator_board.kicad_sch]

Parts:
C1, C2, C3, C4, C5, C6, C7, C8, C9, C10, C11, C12, C13, C14, C15, C16, C17, C18, C19, C20, C21, C22, C23, C24: 10000uf; CP_Radial_D16.0mm_P7.50mm
J1: Conn_01x13_Socket; PinHeader_1x13_P2.54mm_Vertical
J2: Conn_01x02_Pin; AMASS_XT30U-M_1x02_P5.0mm_Vertical
RV1, RV2, RV3, RV4, RV5, RV6, RV7, RV8, RV9, RV10, RV11, RV12: R_Potentiometer; Potentiometer_Bourns_3386W_Horizontal

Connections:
GND: C12.2, C24.2, J1.1, J2.1, RV12.2, RV12.3
unnamed: C11.2, C12.1, C23.2, C24.1, J1.2, RV11.2, RV11.3, RV12.1
unnamed: C10.2, C11.1, C22.2, C23.1, J1.3, RV10.2, RV10.3, RV11.1
unnamed: C9.2, C10.1, C21.2, C22.1, J1.4, RV9.2, RV9.3, RV10.1
unnamed: C8.2, C9.1, C20.2, C21.1, J1.5, RV8.2, RV8.3, RV9.1
unnamed: C7.2, C8.1, C19.2, C20.1, J1.6, RV7.2, RV7.3, RV8.1
unnamed: C6.2, C7.1, C18.2, C19.1, J1.7, RV6.2, RV6.3, RV7.1
unnamed: C5.2, C6.1, C17.2, C18.1, J1.8, RV5.2, RV5.3, RV6.1
unnamed: C4.2, C5.1, C16.2, C17.1, J1.9, RV4.2, RV4.3, RV5.1
unnamed: C3.2, C4.1, C15.2, C16.1, J1.10, RV3.2, RV3.3, RV4.1
unnamed: C2.2, C3.1, C14.2, C15.1, J1.11, RV2.2, RV2.3, RV3.1
unnamed: C1.2, C2.1, C13.2, C14.1, J1.12, RV1.2, RV1.3, RV2.1
VCC: C1.1, C13.1, J1.13, J2.2, RV1.1

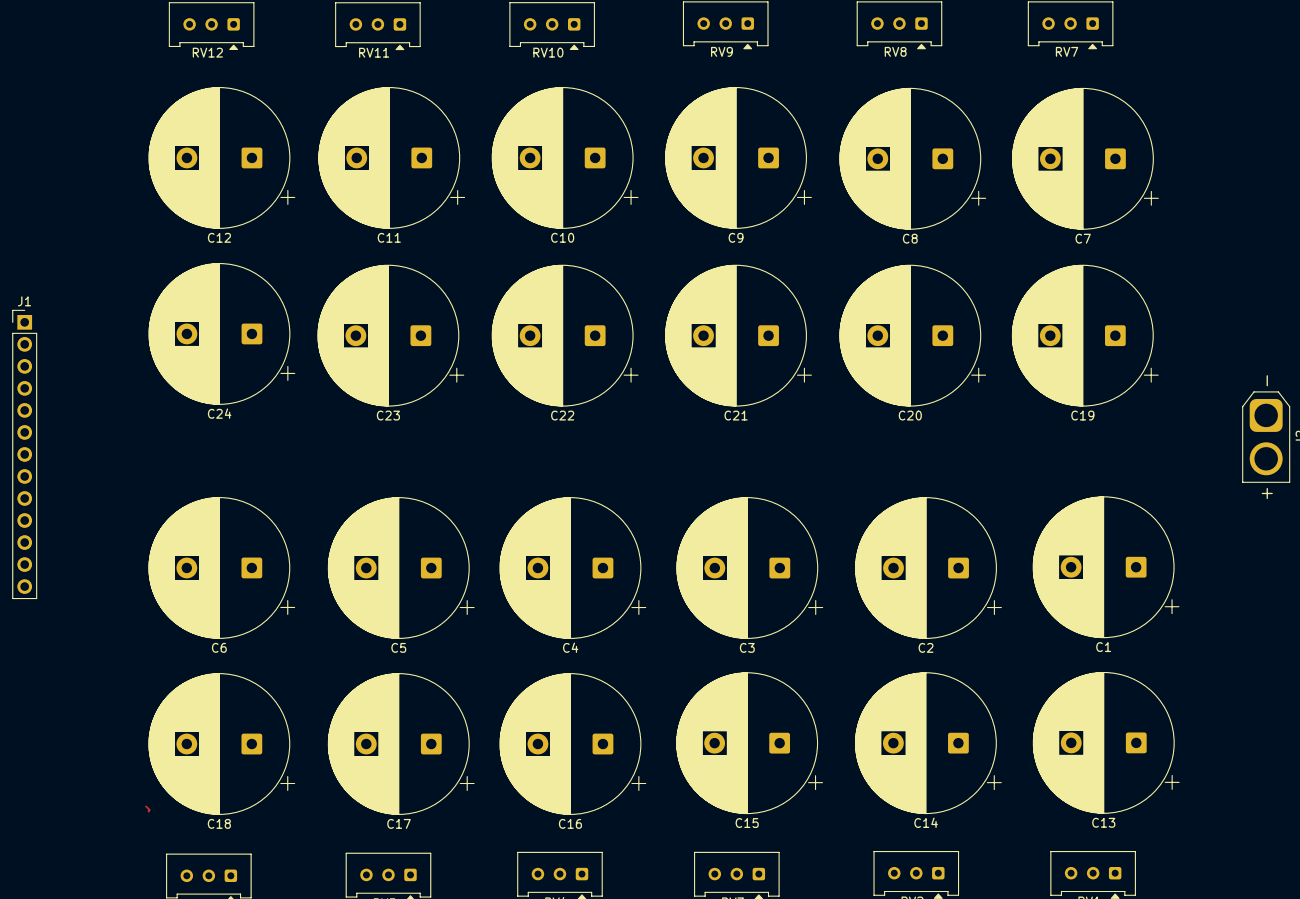
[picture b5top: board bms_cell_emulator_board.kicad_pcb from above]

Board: 2 copper layers, 38 parts (0 on the bottom side), 13 nets.
